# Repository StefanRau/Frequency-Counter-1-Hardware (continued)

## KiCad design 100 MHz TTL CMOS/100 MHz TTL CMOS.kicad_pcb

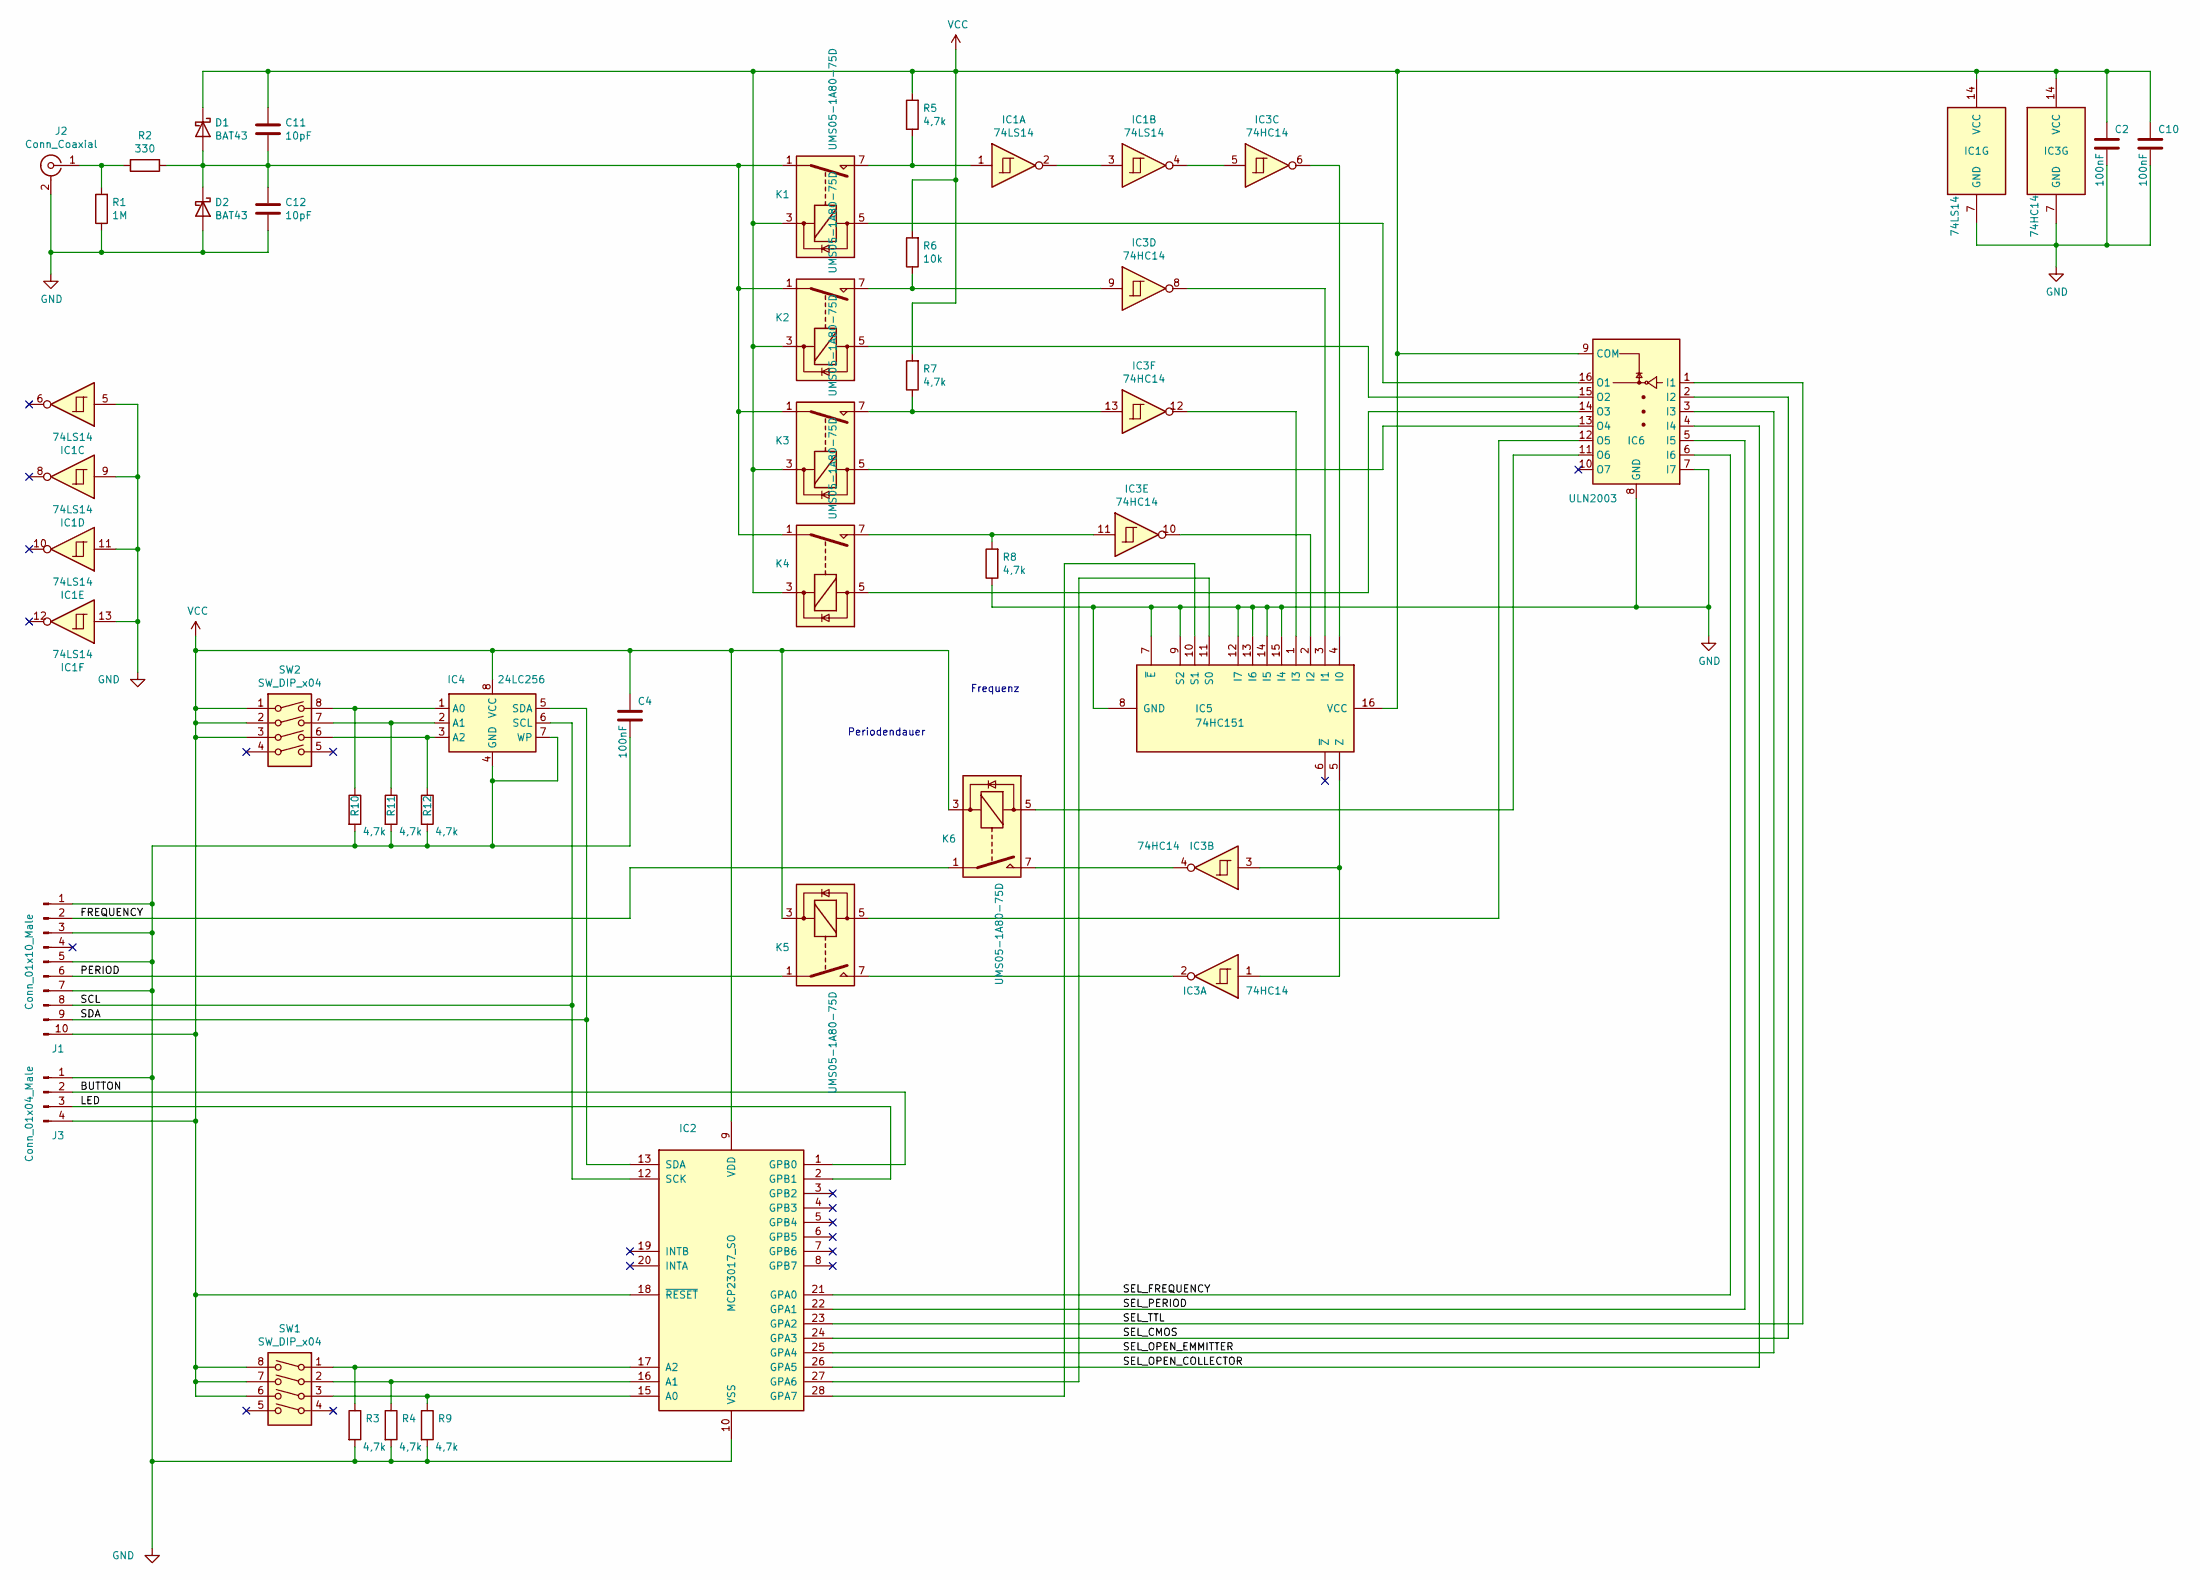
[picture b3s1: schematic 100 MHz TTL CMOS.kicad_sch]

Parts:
C2, C4, C10: 100nF; C_Rect_L10.0mm_W4.0mm_P7.50mm_FKS3_FKP3
C11, C12: 10pF; C_Disc_D4.7mm_W2.5mm_P5.00mm
D1, D2: BAT43; D_DO-35_SOD27_P7.62mm_Horizontal
IC1: 74LS14; DIP-14_W7.62mm_LongPads
IC2: MCP23017_SO; DIP-28_W7.62mm_LongPads
IC3: 74HC14; DIP-14_W7.62mm_LongPads
IC4: 24LC256; DIP-8_W7.62mm_LongPads
IC5: 74HC151; DIP-16_W7.62mm_LongPads
IC6: ULN2003; DIP-16_W7.62mm_LongPads
J1: Conn_01x10_Male; PinHeader_1x10_P2.54mm_Horizontal
J2: Conn_Coaxial; BNC_Amphenol_B6252HB-NPP3G-50_Horizontal
J3: Conn_01x04_Male; PinHeader_1x04_P2.54mm_Vertical
K1, K2, K3, K4, K5, K6: UMS05-1A80-75D; Relay_SPST_StandexMeder_MS_Form1AB
R1: 1M; R_Axial_DIN0207_L6.3mm_D2.5mm_P10.16mm_Horizontal
R2: 330; R_Axial_DIN0207_L6.3mm_D2.5mm_P10.16mm_Horizontal
R3, R4, R9, R10, R11, R12: 4,7k; R_Axial_DIN0204_L3.6mm_D1.6mm_P1.90mm_Vertical
R5, R7, R8: 4,7k; R_Axial_DIN0207_L6.3mm_D2.5mm_P10.16mm_Horizontal
R6: 10k; R_Axial_DIN0207_L6.3mm_D2.5mm_P10.16mm_Horizontal
SW1, SW2: SW_DIP_x04; SW_DIP_SPSTx04_Slide_9.78x12.34mm_W7.62mm_P2.54mm

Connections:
/BUTTON: IC2.1 (GPB0), J3.2
/FREQUENCY: J1.2, K6.1
/LED: IC2.2 (GPB1), J3.3
/PERIOD: J1.6, K5.1
/SCL: IC2.12 (SCK), IC4.6 (SCL), J1.8
/SDA: IC2.13 (SDA), IC4.5 (SDA), J1.9
/SEL_CMOS: IC2.24 (GPA3), IC6.2 (I2)
/SEL_FREQUENCY: IC2.21 (GPA0), IC6.6 (I6)
/SEL_OPEN_COLLECTOR: IC2.26 (GPA5), IC6.4 (I4)
/SEL_OPEN_EMMITTER: IC2.25 (GPA4), IC6.3 (I3)
/SEL_PERIOD: IC2.22 (GPA1), IC6.5 (I5)
/SEL_TTL: IC2.23 (GPA2), IC6.1 (I1)
GND: C2.2, C4.2, C10.2, C12.2, D2.2 (A), IC1.5, IC1.7 (GND), IC1.9, IC1.11, IC1.13, IC2.10 (VSS), IC3.7 (GND), IC4.4 (GND), IC4.7 (WP), IC5.7 (~E), IC5.8 (GND), IC5.9 (S2), IC5.12 (I7), IC5.13 (I6), IC5.14 (I5), IC5.15 (I4), IC6.7 (I7), IC6.8 (GND), J1.1, J1.3, J1.5, J1.7, J2.2 (Ext), J3.1, R1.1, R3.2, R4.2, R8.1, R9.2, R10.2, R11.2, R12.2
unnamed: C11.2, C12.1, D1.2 (A), D2.1 (K), K1.1, K2.1, K3.1, K4.1, R2.1
unnamed: IC1.1, K1.7, R5.1
unnamed: IC1.2, IC1.3
unnamed: IC1.4, IC3.5
unnamed: IC2.15 (A0), R9.1, SW1.3
unnamed: IC2.16 (A1), R4.1, SW1.2
unnamed: IC2.17 (A2), R3.1, SW1.1
unnamed: IC2.27 (GPA6), IC5.11 (S0)
unnamed: IC2.28 (GPA7), IC5.10 (S1)
unnamed: IC3.1, IC3.3, IC5.5 (Z)
unnamed: IC3.2, K5.7
unnamed: IC3.4, K6.7
unnamed: IC3.6, IC5.4 (I0)
unnamed: IC3.8, IC5.3 (I1)
unnamed: IC3.9, K2.7, R6.1
unnamed: IC3.10, IC5.2 (I2)
unnamed: IC3.11, K4.7, R8.2
unnamed: IC3.12, IC5.1 (I3)
unnamed: IC3.13, K3.7, R7.1
unnamed: IC4.1 (A0), R10.1, SW2.8
unnamed: IC4.2 (A1), R11.1, SW2.7
unnamed: IC4.3 (A2), R12.1, SW2.6
unnamed: IC6.11 (O6), K6.5
unnamed: IC6.12 (O5), K5.5
unnamed: IC6.13 (O4), K3.5
unnamed: IC6.14 (O3), K4.5
unnamed: IC6.15 (O2), K2.5
unnamed: IC6.16 (O1), K1.5
unnamed: J2.1 (In), R1.2, R2.2
VCC: C2.1, C4.1, C10.1, C11.1, D1.1 (K), IC1.14 (VCC), IC2.9 (VDD), IC2.18 (~RESET), IC3.14 (VCC), IC4.8 (VCC), IC5.16 (VCC), IC6.9 (COM), J1.10, J3.4, K1.3, K2.3, K3.3, K4.3, K5.3, K6.3, R5.2, R6.2, R7.2, SW1.6, SW1.7, SW1.8, SW2.1, SW2.2, SW2.3

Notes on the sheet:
Periodendauer
Frequenz

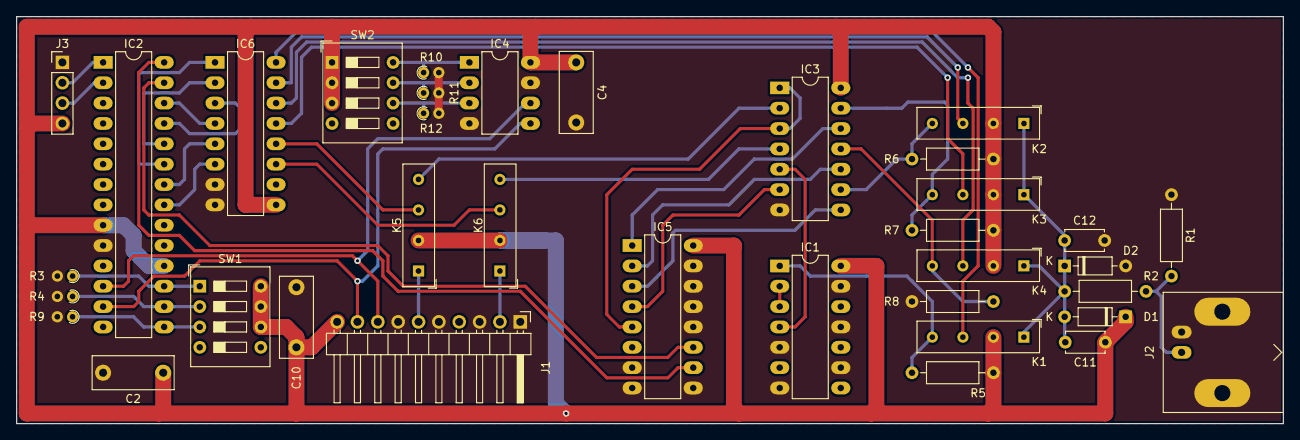
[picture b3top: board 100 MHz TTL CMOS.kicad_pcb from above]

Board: 2 copper layers, 158.1 x 50.8 mm, 36 parts (0 on the bottom side), 43 nets.

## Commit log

2022-08-11 Short break in reset
2022-08-11 Reset Logic updated
2022-09-29 Inserted 3D models into Front Plate
2022-10-02 Update issue templates
2022-10-25 3,3 V compatible inputs
2023-11-08 Update
    Update
